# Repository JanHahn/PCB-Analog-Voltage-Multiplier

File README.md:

# Analog Voltage Multiplier – PCB Project

## 📘 Project Description

This project presents an analog voltage multiplier circuit, designed for low-voltage and low-frequency applications. It is implemented on a two-layer PCB and utilizes the AD633 analog multiplier as its core component.

The circuit is suitable for educational, demonstration, and experimental use in analog electronics.

---

## ⚙️ Design Specifications

- **Input voltage range**: 0 – 2 V  
- **Operating frequency**: 50 Hz  
- **Circuit type**: Analog voltage multiplier  
- **PCB technology**: Two-layer PCB (designed in KiCad)

---

## 🔌 Key Components

| Symbol | Description                         |
|--------|-------------------------------------|
| U2     | AD633 – Analog Multiplier           |
| U3–U8  | TLV2372 – Operational Amplifiers    |
| U1     | LM331 – Voltage-to-Frequency Converter (optional measurement output) |
| IC1    | TPS7A – Voltage Regulator           |
| U11    | TC7660 – Charge Pump (negative voltage generator) |

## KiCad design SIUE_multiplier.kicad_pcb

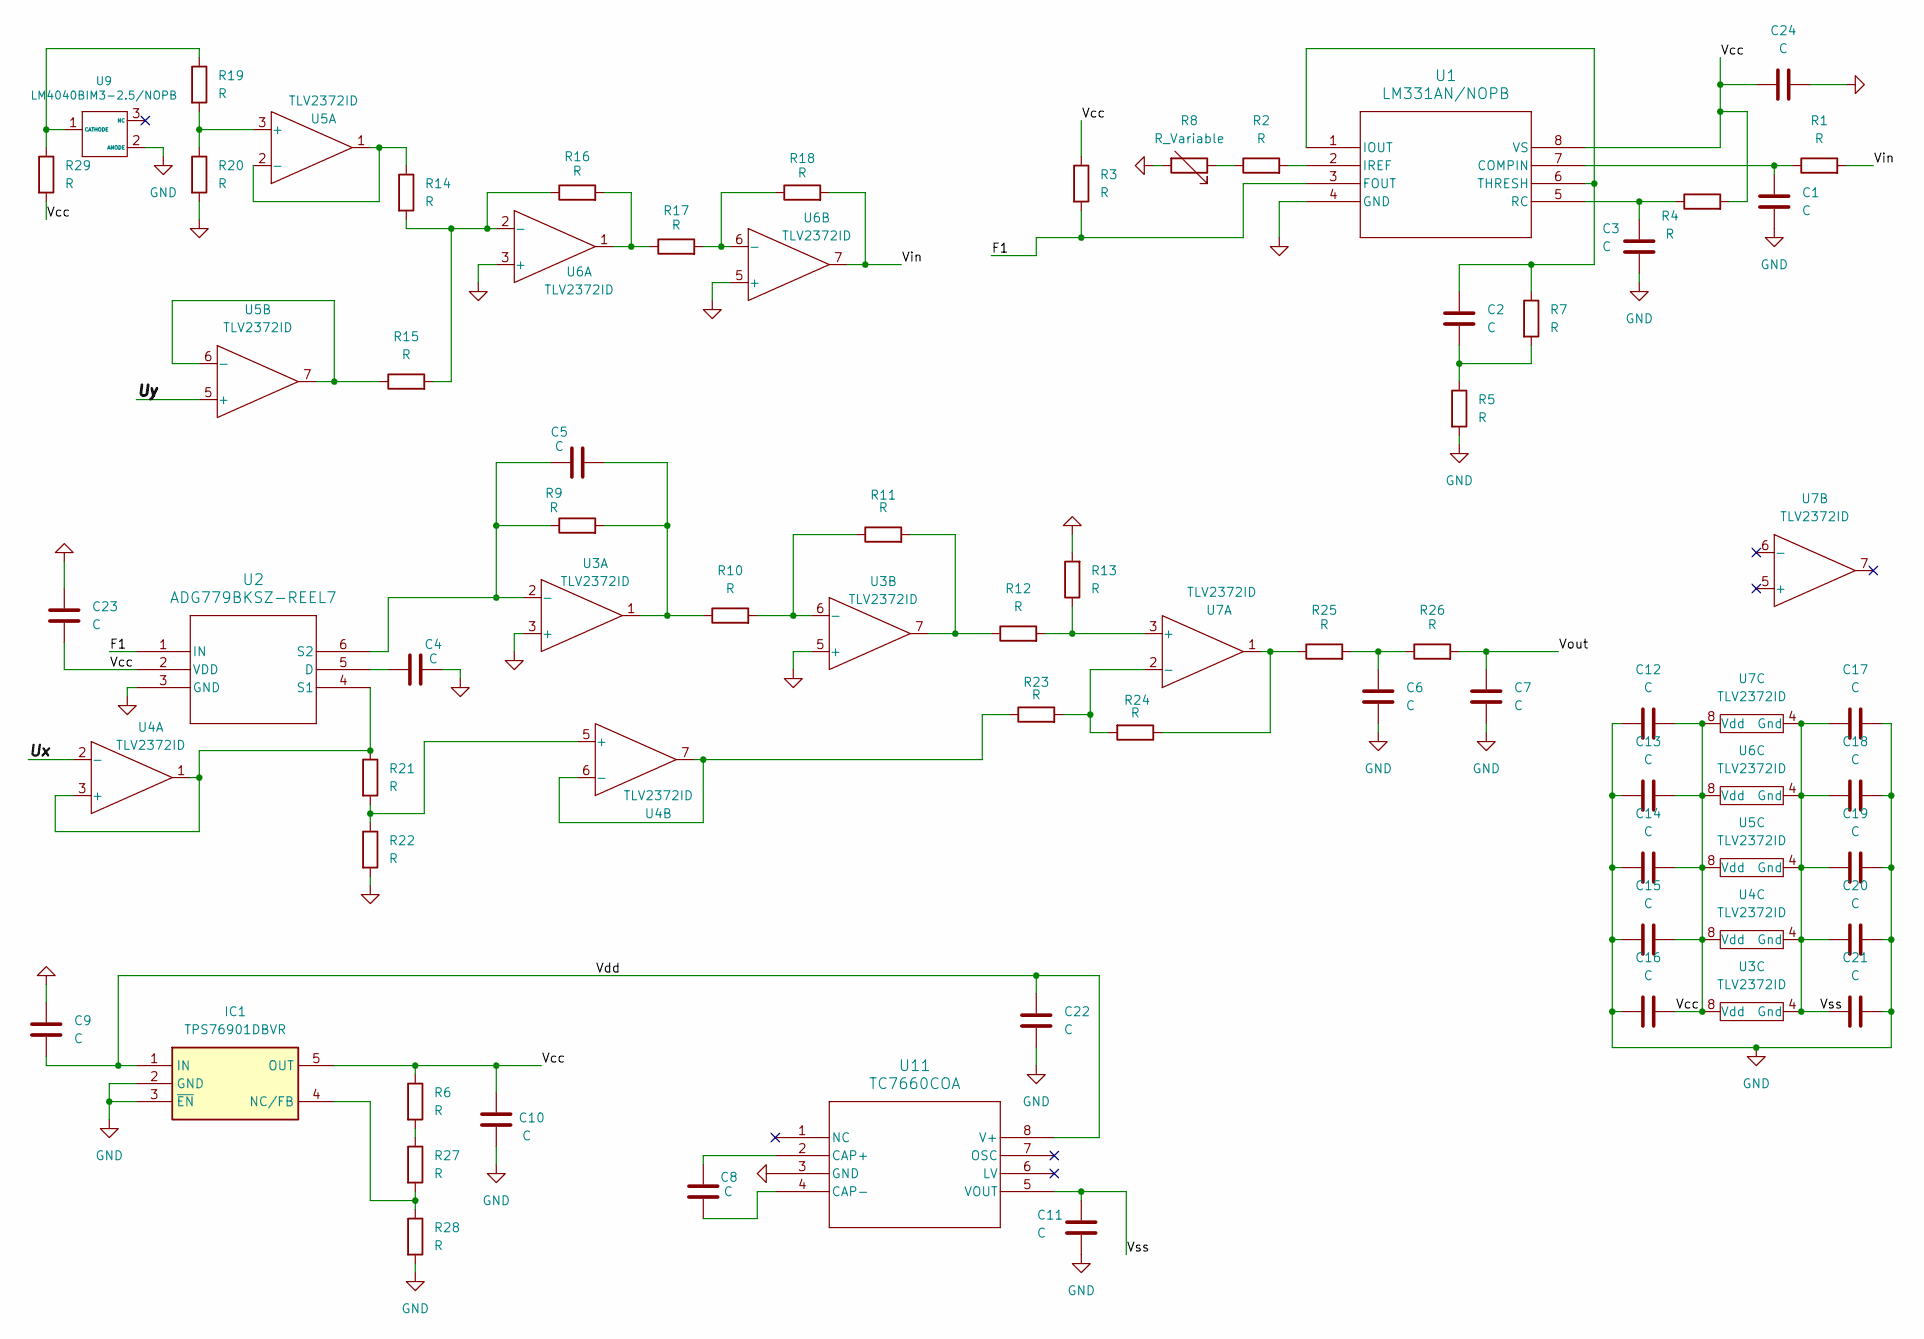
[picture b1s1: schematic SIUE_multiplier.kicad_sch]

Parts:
C1, C2, C3, C4, C5, C6, C7, C8, C10, C11, C12, C13, C14, C15, C16, C17, C18, C19, C20, C21, C22, C23, C24: C; C_0805_2012Metric_Pad1.18x1.45mm_HandSolder
C9: C; CP_EIA-3528-21_Kemet-B_Pad1.50x2.35mm_HandSolder
IC1: TPS76901DBVR; TPS6901DBVR; Manufacturer_Part_Number TPS76901DBVR
R1, R2, R3, R4, R5, R6, R7, R9, R10, R11, R12, R13, R14, R15, R16, R17, R18, R19, R20, R21, R22, R23, R24, R25, R26, R27, R28, R29: R; R_0805_2012Metric_Pad1.20x1.40mm_HandSolder
R8: R_Variable; Potentiometer_Bourns_3296W_Vertical
U1: LM331AN/NOPB; LM331_ofc
U2: ADG779BKSZ-REEL7; KS_6_ADI
U3, U4, U5, U6, U7: TLV2372ID; TLV2372_D8-L
U9: LM4040BIM3-2.5/NOPB; LM4040
U11: TC7660COA

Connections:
/F1: R3.2, U1.3 (FOUT), U2.1 (IN)
/Ux: U4.2 (-)
/Uy: U5.5 (+)
/Vcc: C10.1, C12.2, C13.2, C14.2, C15.2, C16.2, C23.1, C24.1, IC1.5 (OUT), R3.1, R4.2, R6.1, R29.2, U1.8 (VS), U2.2 (VDD), U3.8 (Vdd), U4.8 (Vdd), U5.8 (Vdd), U6.8 (Vdd), U7.8 (Vdd)
/Vdd: C9.1, C22.1, IC1.1 (IN), U11.8 (V+)
/Vin: R1.2, R18.2, U6.7
/Vout: C7.1, R26.2
/Vss: C11.1, C17.1, C18.1, C19.1, C20.1, C21.1, U3.4 (Gnd), U4.4 (Gnd), U5.4 (Gnd), U6.4 (Gnd), U7.4 (Gnd), U11.5 (VOUT)
GND: C1.2, C3.2, C4.2, C6.2, C7.2, C9.2, C10.2, C11.2, C12.1, C13.1, C14.1, C15.1, C16.1, C17.2, C18.2, C19.2, C20.2, C21.2, C22.2, C23.2, C24.2, IC1.2 (GND), IC1.3 (~EN), R5.2, R8.2, R13.2, R20.2, R22.2, R28.2, U1.4 (GND), U2.3 (GND), U3.3 (+), U3.5 (+), U6.3 (+), U6.5 (+), U9.2 (ANODE), U11.3 (GND)
unnamed: C2.2, R5.1, R7.2
unnamed: C5.2, R9.2, R10.1, U3.1
unnamed: C6.1, R25.2, R26.1
unnamed: IC1.4 (NC/FB), R27.2, R28.1
unnamed: R2.1, R8.1
unnamed: R11.2, R12.1, U3.7
unnamed: R16.2, R17.1, U6.1
unnamed: R24.1, R25.1, U7.1
unnamed: R6.2, R27.1
unnamed: C1.1, R1.1, U1.7 (COMPIN)
unnamed: C2.1, R7.1, U1.1 (IOUT), U1.6 (THRESH)
unnamed: R2.2, U1.2 (IREF)
unnamed: C3.1, R4.1, U1.5 (RC)
unnamed: C4.1, U2.5 (D)
unnamed: R21.1, U2.4 (S1), U4.1, U4.3 (+)
unnamed: C5.1, R9.1, U2.6 (S2), U3.2 (-)
unnamed: R10.2, R11.1, U3.6 (-)
unnamed: R21.2, R22.1, U4.5 (+)
unnamed: R23.1, U4.6 (-), U4.7
unnamed: R19.2, R20.1, U5.3 (+)
unnamed: R14.1, U5.1, U5.2 (-)
unnamed: R15.1, U5.6 (-), U5.7
unnamed: R14.2, R15.2, R16.1, U6.2 (-)
unnamed: R17.2, R18.1, U6.6 (-)
unnamed: R12.2, R13.1, U7.3 (+)
unnamed: R23.2, R24.2, U7.2 (-)
unnamed: R19.1, R29.1, U9.1 (CATHODE)
unnamed: C8.1, U11.2 (CAP+)
unnamed: C8.2, U11.4 (CAP-)

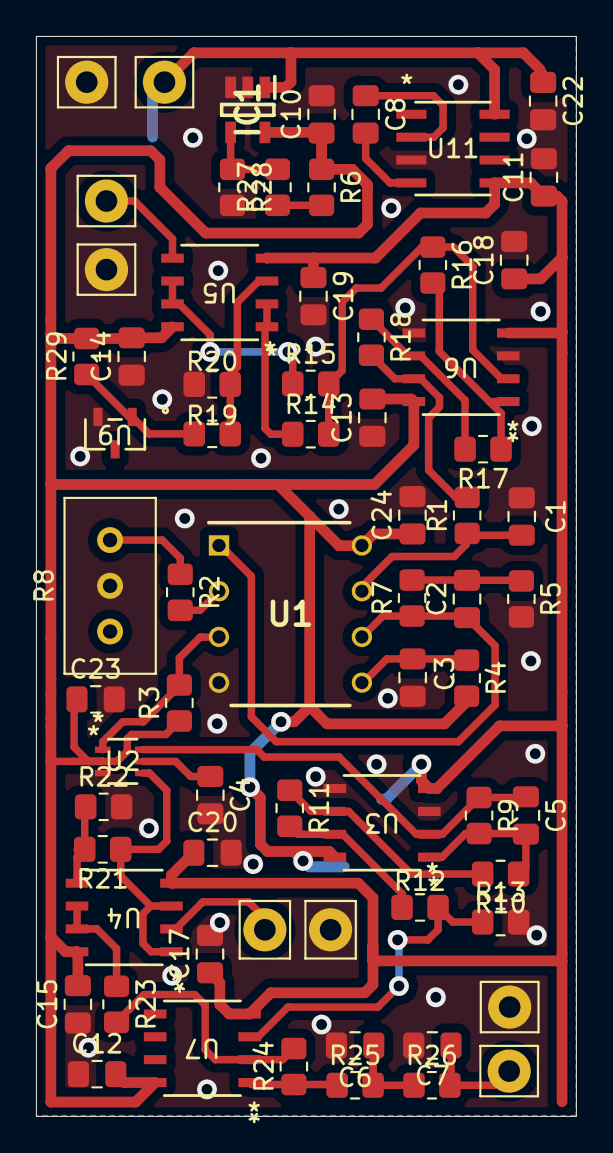
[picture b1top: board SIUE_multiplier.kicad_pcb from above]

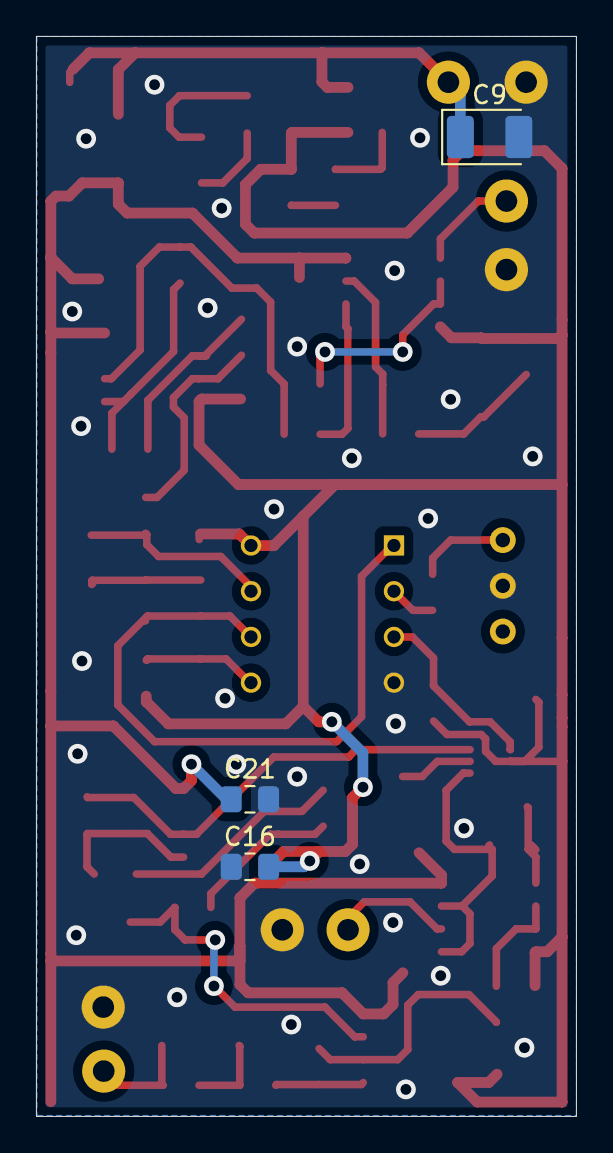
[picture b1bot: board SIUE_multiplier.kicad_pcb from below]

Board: 2 copper layers, 30.0 x 60.0 mm, 63 parts (3 on the bottom side), 36 nets.
